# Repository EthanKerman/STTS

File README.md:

# STTS — Pocket Synth

A **behbeh** credit card sized synth for your wallet. The keys are a full octave ad you can go up and down 2 more. The noise from a piezo disc which is why theres a hole in the board.

## Features (this feels like a sales pitch lol)

- 13 touch keys (C to high C), octave down, octave up, and mode
- Three play modes of plain, arpeggio, vibrato
- Octave shift of ±2
- Differential piezo drive for hopefully double the volume of a normal buzzer
- Runs on one CR2016 coin cell, auto sleeps after 30 s, hold MODE to wake

## How it works

- **MCU:** ATtiny1617 (24 pin QFN), programmed over UPDI
- **Touch sensing:** each key is a copper pad under soldermask, connected to a MCU pin and to a shared TOUCH_SEND line on a 1 MΩ resistor. The firmware times how long each pad takes to charge a finger adds capacitance and makes it slower. Each pad is calibrated at power on.
- **Speaker:** a 15 mm piezo disc glued over a 10 mm hole, driven from two pins in opposite phase. Touch readings are timed between speaker transitions to avoid interference.
- **Power:** CR2016 → B5819W Schottky diode (blocks the programmer from back feeding the coin cell) → 10 µF + 100 nF decoupling.
- **Layout:** all components are on the back. Nothing sits behind the white keys, and no key's trace runs behind a different key, to keep keys from triggering each other.

## Repo layout

| Folder | Contents |

| `hardware/` | KiCad 9 project (schematic, PCB, custom footprints in `libs/`) |
| `firmware/STTS/` | Arduino sketch (megaTinyCore) |
| `production/` | Gerbers, BOM, and placement (CPL) files for JLCPCB |
| `images/` | Beautiful renders and screenshots |

## Bill of materials

Assembled by JLCPCB (Economic PCBA, bottom side), 5 boards.

Full BOM: bom.csv

Assembled by JLCPCB (Economic PCBA, bottom side), 5 boards.

Part	Qty per board	LCSC
ATtiny1617-MNR	1	C614176
1 MΩ 0603 resistor	16	C22935
10 µF 0805 capacitor	1	C15850
100 nF 0603 capacitor	1	C14663
B5819W Schottky diode	1	C8598
CR2016 SMD holder	1	C964740
15 mm piezo disc (hand-soldered)	1	—
Item	Cost (USD)
JLCPCB order (5 PCBs, assembly, components, shipping)	$52.12
Piezo discs	$5.00
3D-printed case (own printers)	$0.00
Total	$57.12

**JLCPCB quote (5 assembled boards, 0.8 mm): $52.12**

**Piezo discs (bought separately): $5**

**Total: $57.12**

## Building and flashing

1. Install the Arduino IDE and add **megaTinyCore** through the Boards Manager.
2. Settings: Chip **ATtiny1617**, Clock **5 MHz internal**, millis() timer **TCA0 or TCD0** (not TCB0, which drives the speaker), Programmer **SerialUPDI**.
3. Wire a 3.3 V USB serial adapter as a SerialUPDI programmer to the GND / UPDI / VCC pads on the back. **Take the coin cell out before connecting VCC.**
4. Run **Burn Bootloader** once to set the clock fuses, then **Upload**.

## Status

Schematic                                        yeye
PCB layout (DRC clean)                           yeye
Firmware v0.1 (compiles untested on hardware)    yeye
Front and back 3d printed covers                 yeye
Boards ordered                                   nono
Bring up and touch tuning                        nono

## Case

A two-piece 3D-printed case: the bottom piece holds the card, and the top piece slides on after it's in. There's also a bottom-only version that works as a back cover. The piezo has a clear window so it can still vibrate, and the touch keys stay exposed.

- STLs and STEP: `case/`
- Editable Onshape source: [Onshape document](https://cad.onshape.com/documents/209f1cf692407caf204aedcd/w/ec89c730faa0e29024759e87/e/6a25621725d754ed044dea4a)

## Notes

Designed by yours truly EthanKerman for [Hack Club Forge](https://forge.hackclub.com)

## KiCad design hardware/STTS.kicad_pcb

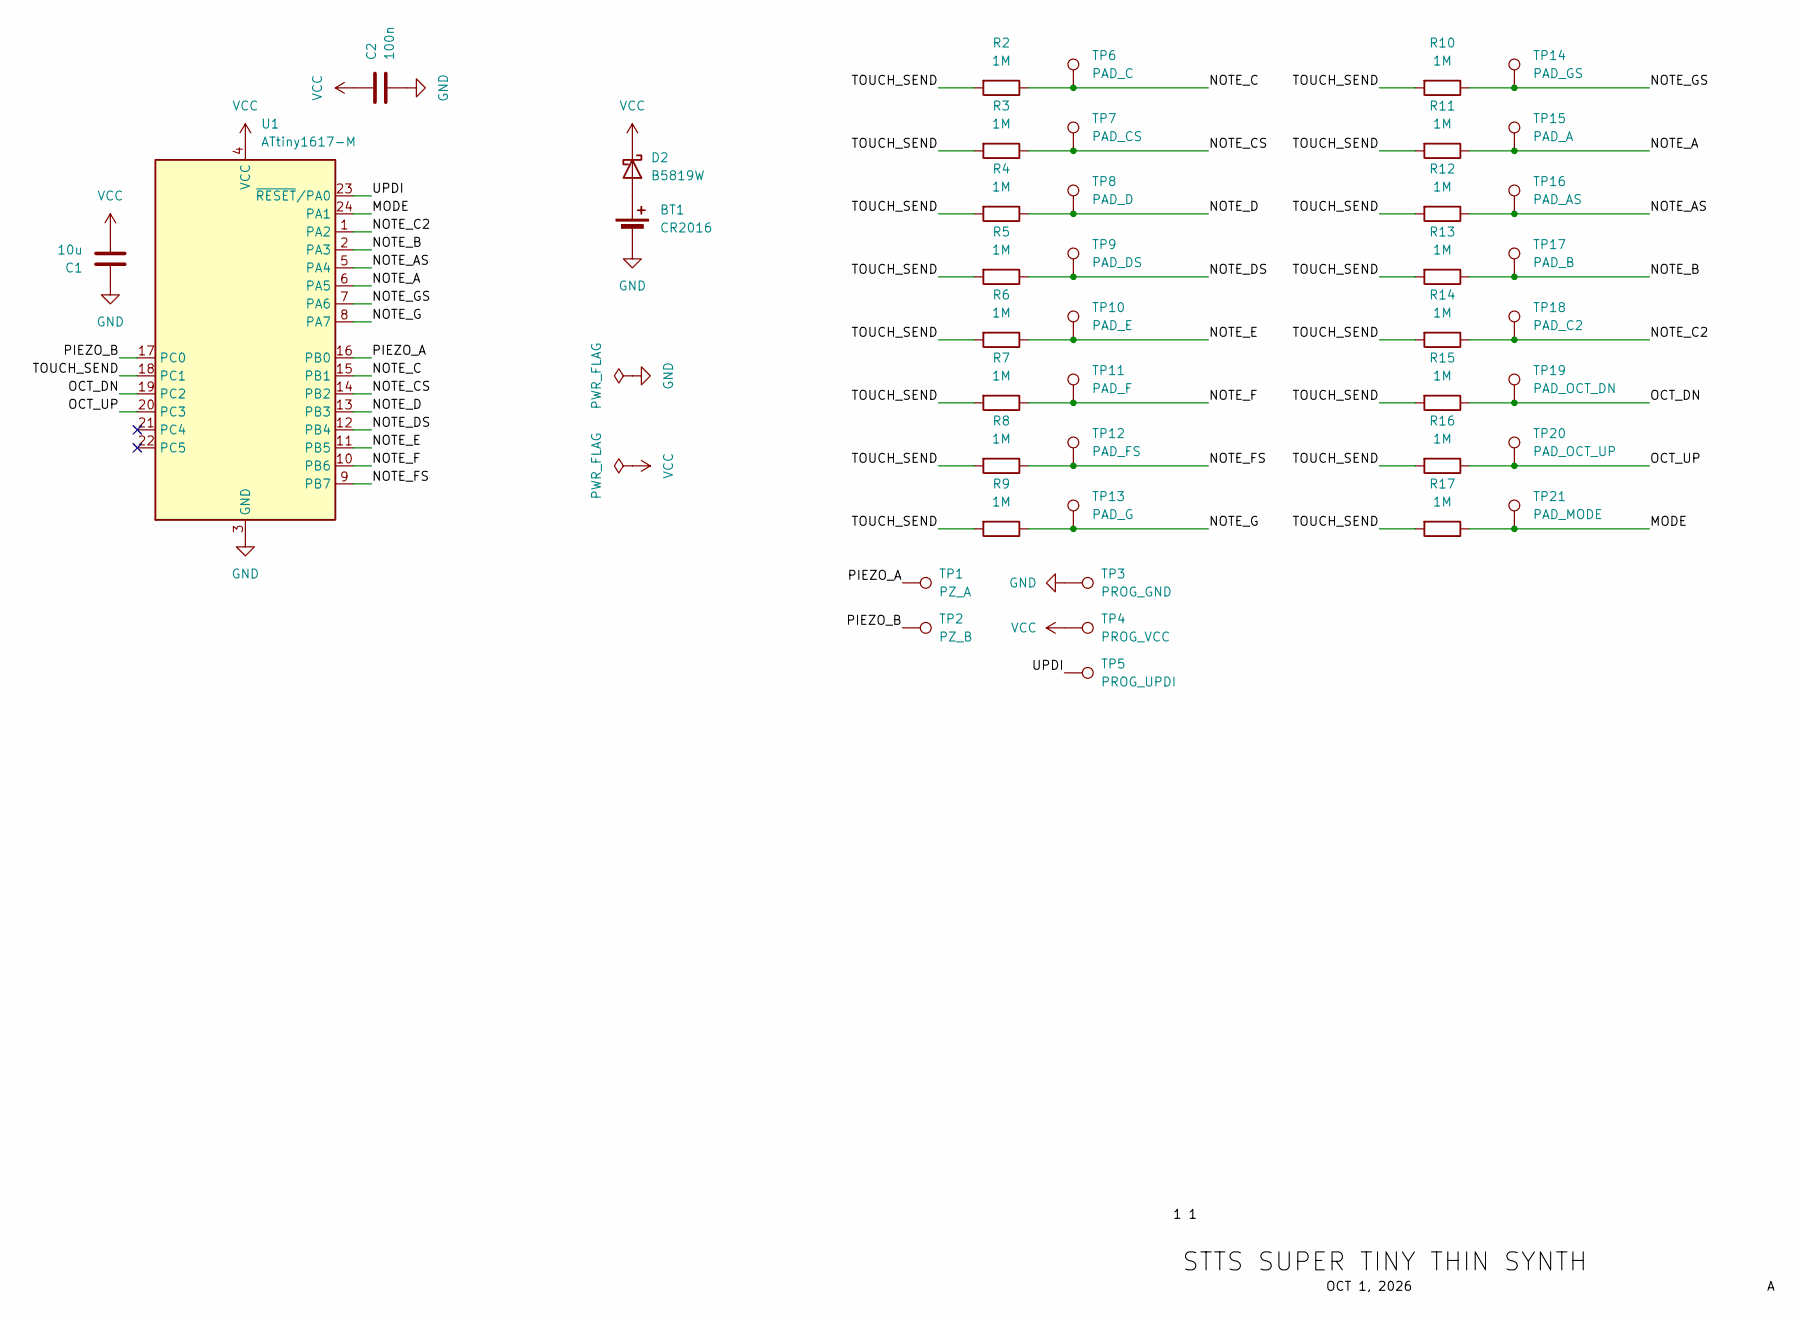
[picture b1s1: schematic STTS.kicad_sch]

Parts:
BT1: CR2016; BAT-SMD_BS-2016-B2AA001; LCSC C964740
C1: 10u; C_0805_2012Metric; LCSC C15850
C2: 100n; C_0603_1608Metric; LCSC C14663
D2: B5819W; D_SOD-123; LCSC C8598
R2, R3, R4, R5, R6, R7, R8, R9, R10, R11, R12, R13, R14, R15, R16, R17: 1M; R_0603_1608Metric; LCSC C22935
TP1: PZ_A; TestPoint_Pad_D2.0mm
TP2: PZ_B; TestPoint_Pad_D2.0mm
TP3: PROG_GND; TestPoint_Pad_D1.5mm
TP4: PROG_VCC; TestPoint_Pad_D1.5mm
TP5: PROG_UPDI; TestPoint_Pad_D1.5mm
TP6: PAD_C; TouchPad_White
TP7: PAD_CS; TouchPad_Black
TP8: PAD_D; TouchPad_White
TP9: PAD_DS; TouchPad_Black
TP10: PAD_E; TouchPad_White
TP11: PAD_F; TouchPad_White
TP12: PAD_FS; TouchPad_Black
TP13: PAD_G; TouchPad_White
TP14: PAD_GS; TouchPad_Black
TP15: PAD_A; TouchPad_White
TP16: PAD_AS; TouchPad_Black
TP17: PAD_B; TouchPad_White
TP18: PAD_C2; TouchPad_White
TP19: PAD_OCT_DN; TouchPad_Func
TP20: PAD_OCT_UP; TouchPad_Func
TP21: PAD_MODE; TouchPad_Func
U1: ATtiny1617-M; QFN-24-1EP_4x4mm_P0.5mm_EP2.6x2.6mm; LCSC C614176

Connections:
/MODE: R17.1, TP21.1, U1.24 (PA1)
/NOTE_A: R11.1, TP15.1, U1.6 (PA5)
/NOTE_AS: R12.1, TP16.1, U1.5 (PA4)
/NOTE_B: R13.1, TP17.1, U1.2 (PA3)
/NOTE_C: R2.1, TP6.1, U1.15 (PB1)
/NOTE_C2: R14.1, TP18.1, U1.1 (PA2)
/NOTE_CS: R3.1, TP7.1, U1.14 (PB2)
/NOTE_D: R4.1, TP8.1, U1.13 (PB3)
/NOTE_DS: R5.1, TP9.1, U1.12 (PB4)
/NOTE_E: R6.1, TP10.1, U1.11 (PB5)
/NOTE_F: R7.1, TP11.1, U1.10 (PB6)
/NOTE_FS: R8.1, TP12.1, U1.9 (PB7)
/NOTE_G: R9.1, TP13.1, U1.8 (PA7)
/NOTE_GS: R10.1, TP14.1, U1.7 (PA6)
/OCT_DN: R15.1, TP19.1, U1.19 (PC2)
/OCT_UP: R16.1, TP20.1, U1.20 (PC3)
/PIEZO_A: TP1.1, U1.16 (PB0)
/PIEZO_B: TP2.1, U1.17 (PC0)
/TOUCH_SEND: R2.2, R3.2, R4.2, R5.2, R6.2, R7.2, R8.2, R9.2, R10.2, R11.2, R12.2, R13.2, R14.2, R15.2, R16.2, R17.2, U1.18 (PC1)
/UPDI: TP5.1, U1.23 (~RESET/PA0)
GND: BT1.2 (-), C1.2, C2.2, TP3.1, U1.3 (GND), U1.25 (GND)
unnamed: BT1.1 (+), D2.2 (A)
VCC: C1.1, C2.1, D2.1 (K), TP4.1, U1.4 (VCC)

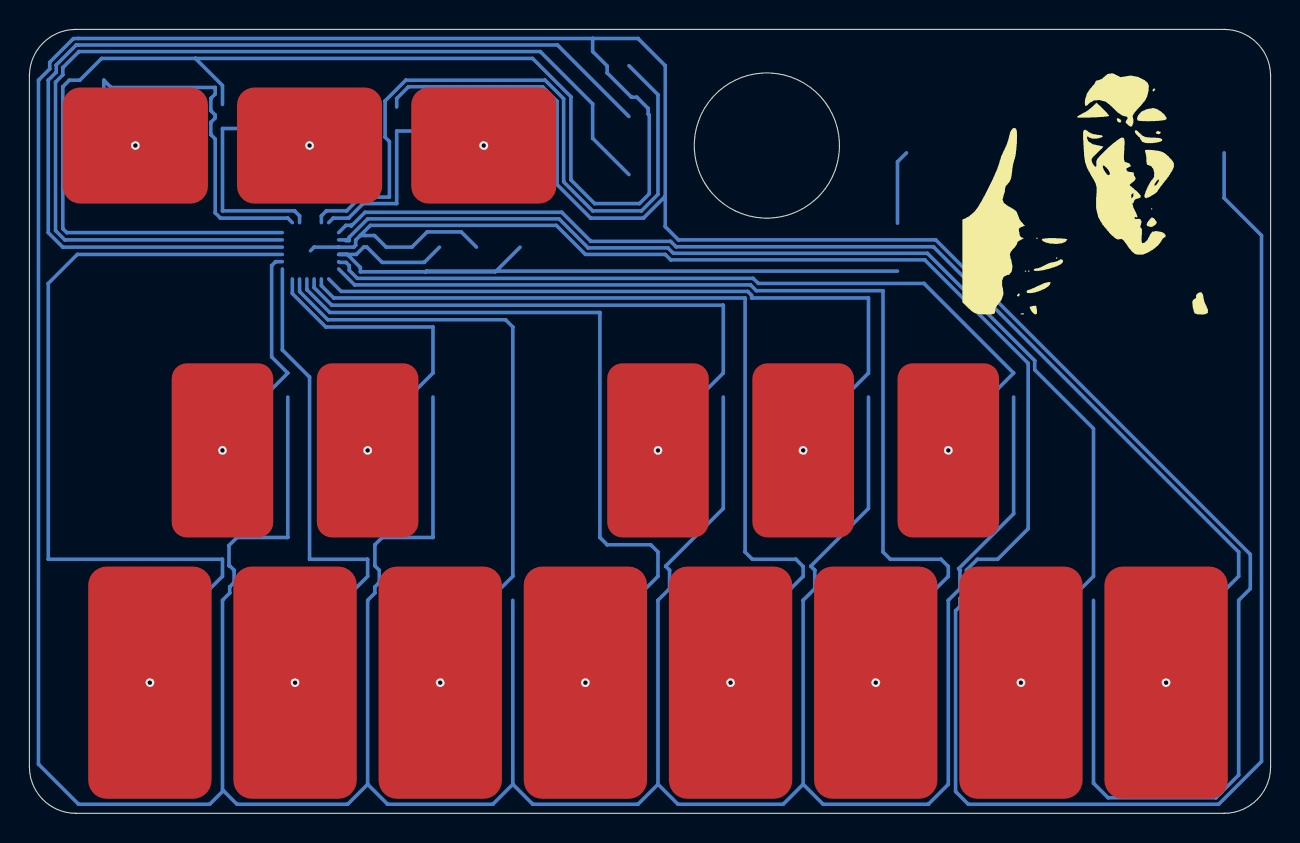
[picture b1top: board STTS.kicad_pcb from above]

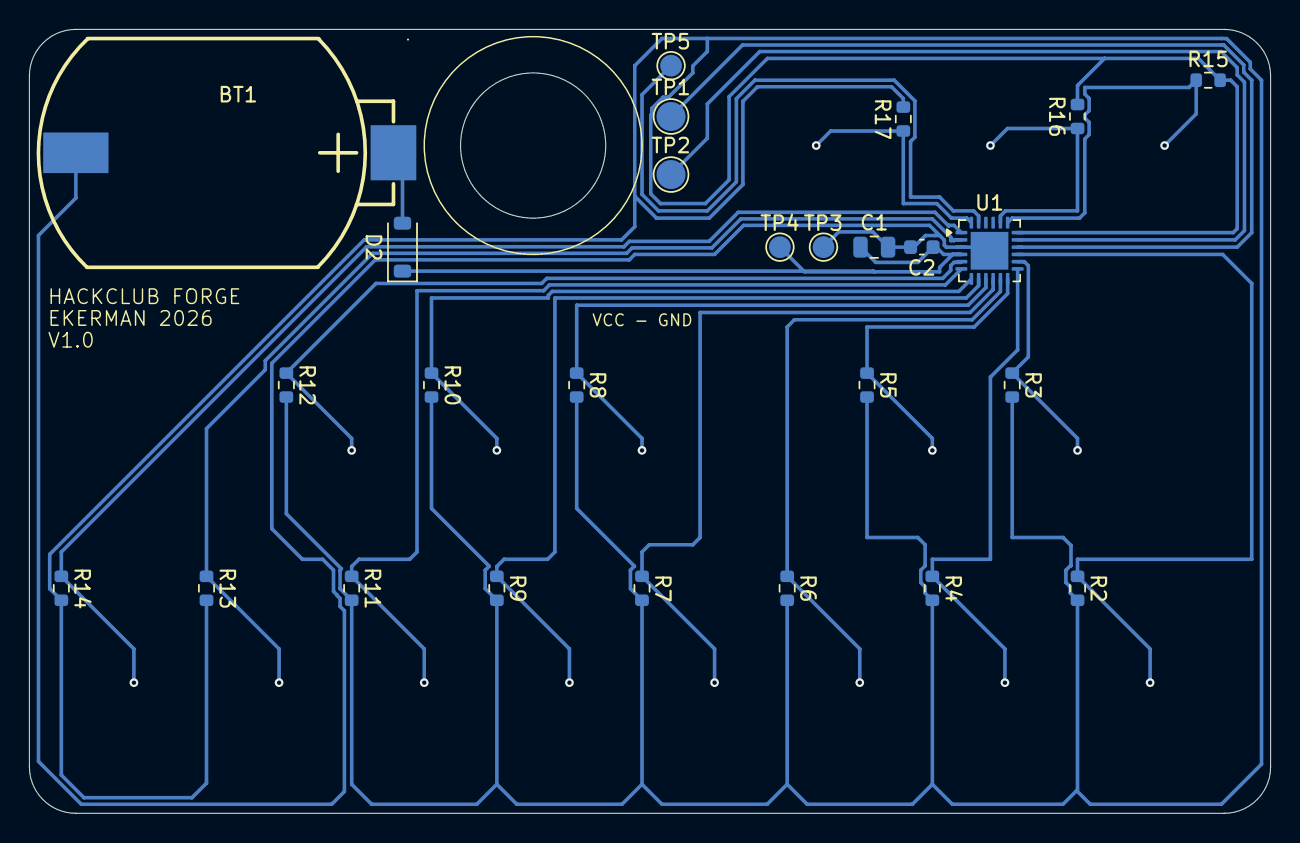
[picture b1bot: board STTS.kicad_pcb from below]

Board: 2 copper layers, 85.5 x 54.0 mm, 42 parts (26 on the bottom side), 23 nets.

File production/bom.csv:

Designator,Footprint,Quantity,Value,LCSC Part #
BT1,BAT-SMD_BS-2016-B2AA001,1,CR2016,C964740
C1,0805,1,10u,C15850
C2,0603,1,100n,C14663
D2,D_SOD-123,1,B5819W,C8598
"R10, R11, R12, R13, R14, R15, R16, R17, R2, R3, R4, R5, R6, R7, R8, R9",0603,16,1M,C22935
U1,QFN-24-1EP_4x4mm_P0.5mm_EP2.6x2.6mm,1,ATtiny1617-M,C614176

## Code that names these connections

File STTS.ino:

//         ___________________________________________________________________________________________
//        /                  |                         |                           /                  |
//       /                   |                         |                          /                   |
//      /                    |                         |                         /                    |
//     /              _______|_______           _______|_______         ________/              _______|
//    /              |               |         |              |         |      /              |
//    |              |_______        |         |              |         |      |              |_______       
//    |                      |       |         |              |         |      |                      |
//    |________              |       |         |              |         |      |________              |
//             |             |       |         |              |         |               |             |
//    _________|             /       |         |              |         |       ________|             /
//    |                     /        |         |              |         |      |                     /
//    |                    /         |         |              |         |      |                    /
//    |                   /          |         |              |         |      |                   /          STTS pocket synth firmware
//    |__________________/           |_________|              |_________|      |__________________/           v0.1

// ---------- Pins ----------
struct Pad {
  VPORT_t *vp;   
  uint8_t m;     
};


const Pad pads[16] = {
  {&VPORTB, PIN1_bm},  // 0  C
  {&VPORTB, PIN2_bm},  // 1  C#
  {&VPORTB, PIN3_bm},  // 2  D
  {&VPORTB, PIN4_bm},  // 3  D#
  {&VPORTB, PIN5_bm},  // 4  E
  {&VPORTB, PIN6_bm},  // 5  F
  {&VPORTB, PIN7_bm},  // 6  F#
  {&VPORTA, PIN7_bm},  // 7  G
  {&VPORTA, PIN6_bm},  // 8  G#
  {&VPORTA, PIN5_bm},  // 9  A
  {&VPORTA, PIN4_bm},  // 10 A#
  {&VPORTA, PIN3_bm},  // 11 B
  {&VPORTA, PIN2_bm},  // 12 high C
  {&VPORTC, PIN2_bm},  // 13 OCT_DN
  {&VPORTC, PIN3_bm},  // 14 OCT_UP
  {&VPORTA, PIN1_bm},  // 15 MODE
};

#define NUM_PADS   16
#define NUM_KEYS   13
#define PAD_OCT_DN 13
#define PAD_OCT_UP 14
#define PAD_MODE   15

#define SEND_M   PIN1_bm  
#define PIEZO_A  PIN0_bm   
#define PIEZO_B  PIN0_bm 

// ---------- Settings ----------
#define SAMPLES   16         
#define TIMEOUT   1000     
#define SLEEP_MS  30000UL    

// ---------- State ----------
volatile bool soundOn = false;
uint16_t baseline[NUM_PADS];
int8_t octave = 0;          
uint8_t mode = 0;           
uint32_t lastTouch = 0;
bool prevFn[3] = {false, false, false};


const uint16_t freq100[12] = {
  26163, 27718, 29366, 31113, 32963, 34923,
  36999, 39200, 41530, 44000, 46616, 49388
};

// ================= SPEAKER =================


ISR(TCB0_INT_vect) {
  TCB0.INTFLAGS = TCB_CAPT_bm;
  VPORTB.IN = PIEZO_A;  
  VPORTC.IN = PIEZO_B;
}

uint16_t ticksFor(int8_t semis) {      
  int8_t oct = 0;
  while (semis < 0)   { semis += 12; oct--; }
  while (semis >= 12) { semis -= 12; oct++; }
  uint32_t t = (F_CPU / 4) * 100UL / freq100[(uint8_t)semis];
  if (oct > 0) t >>= oct;
  if (oct < 0) t <<= -oct;
  if (t > 65000) t = 65000;
  if (t < 100) t = 100;
  return (uint16_t)t;
}

void soundStart(uint16_t ticks) {
  if (!soundOn) {
    VPORTB.OUT |= PIEZO_A;    
    VPORTC.OUT &= ~PIEZO_B;
    TCB0.CCMP = ticks;
    TCB0.CNT = 0;
    TCB0.INTCTRL = TCB_CAPT_bm;
    TCB0.CTRLA = TCB_CLKSEL_CLKDIV2_gc | TCB_ENABLE_bm;
    soundOn = true;
  } else {
    cli();
    TCB0.CCMP = ticks;
    if (TCB0.CNT >= ticks) TCB0.CNT = 0;
    sei();
  }
}

void soundStop() {
  TCB0.CTRLA = 0;
  TCB0.INTCTRL = 0;
  soundOn = false;
  VPORTB.OUT &= ~PIEZO_A;
  VPORTC.OUT &= ~PIEZO_B;
}

// ================= TOUCH =================

void waitQuiet() {
  if (!soundOn) return;
  if (TCB0.CCMP < 450) return;   
  while (true) {
    uint16_t c = TCB0.CNT;
    uint16_t top = TCB0.CCMP;
    if (c > 150 && (uint16_t)(top - c) > 250) return;
  }
}

uint16_t sensePad(uint8_t i) {
  VPORT_t *vp = pads[i].vp;
  uint8_t m = pads[i].m;
  uint16_t total = 0;

  for (uint8_t s = 0; s < SAMPLES; s++) {
    waitQuiet();
    cli();
    VPORTC.OUT &= ~SEND_M;    
    vp->OUT &= ~m;                  
    vp->DIR |= m;
    delayMicroseconds(4);
    vp->DIR &= ~m;              

    uint16_t t = 0;
    VPORTC.OUT |= SEND_M;         
    while (!(vp->IN & m) && t < TIMEOUT) t++;
    vp->OUT |= m;                 
    vp->DIR |= m;
    vp->DIR &= ~m;
    vp->OUT &= ~m;
    VPORTC.OUT &= ~SEND_M;          
    while ((vp->IN & m) && t < 2 * TIMEOUT) t++;
    sei();

    total += t;
  }
  return total;
}

uint16_t threshold(uint8_t i) {
  return baseline[i] / 8 + 8;       
}

void calibrate() {
  for (uint8_t i = 0; i < NUM_PADS; i++) baseline[i] = sensePad(i);
  for (uint8_t k = 0; k < 7; k++) {
    for (uint8_t i = 0; i < NUM_PADS; i++) {
      baseline[i] = (uint16_t)(((uint32_t)baseline[i] * 3 + sensePad(i)) / 4);
    }
  }
}

// ================= SLEEP =================

ISR(RTC_PIT_vect) {
  RTC.PITINTFLAGS = RTC_PI_bm;    
}

void goToSleep() {
  soundStop();

  VPORTC.OUT &= ~SEND_M;
  for (uint8_t i = 0; i < NUM_PADS; i++) {
    pads[i].vp->OUT &= ~pads[i].m;
    pads[i].vp->DIR |= pads[i].m;
  }

  // Baseline for MODE with the other pads held low
  pads[PAD_MODE].vp->DIR &= ~pads[PAD_MODE].m;
  uint16_t sleepBase = sensePad(PAD_MODE);
  uint16_t sleepThr = sleepBase / 8 + 8;
  pads[PAD_MODE].vp->DIR |= pads[PAD_MODE].m;

  while (RTC.STATUS > 0) {}
  RTC.CLKSEL = RTC_CLKSEL_INT32K_gc;
  while (RTC.PITSTATUS > 0) {}
  RTC.PITINTCTRL = RTC_PI_bm;
  RTC.PITCTRLA = RTC_PERIOD_CYC8192_gc | RTC_PITEN_bm;

  uint8_t hits = 0;
  while (hits < 2) {              
    SLPCTRL.CTRLA = SLPCTRL_SMODE_PDOWN_gc | SLPCTRL_SEN_bm;
    __asm__ __volatile__("sleep");
    SLPCTRL.CTRLA = 0;

    pads[PAD_MODE].vp->DIR &= ~pads[PAD_MODE].m;
    uint16_t r = sensePad(PAD_MODE);
    pads[PAD_MODE].vp->DIR |= pads[PAD_MODE].m;

    if (r > sleepBase + sleepThr) hits++;
    else hits = 0;
  }

  // Awake again
  while (RTC.PITSTATUS > 0) {}
  RTC.PITCTRLA = 0;
  for (uint8_t i = 0; i < NUM_PADS; i++) {
    pads[i].vp->DIR &= ~pads[i].m; 
  }
  prevFn[2] = true;               
  lastTouch = millis();

  soundStart(ticksFor(12));          
  delay(60);
  soundStop();
}

// ================= MAIN =================

void setup() {
  VPORTC.DIR |= SEND_M;
  VPORTC.OUT &= ~SEND_M;
  VPORTB.DIR |= PIEZO_A;
  VPORTC.DIR |= PIEZO_B;
  PORTC.PIN4CTRL = PORT_PULLUPEN_bm; 
  PORTC.PIN5CTRL = PORT_PULLUPEN_bm;
  for (uint8_t i = 0; i < NUM_PADS; i++) {
    pads[i].vp->DIR &= ~pads[i].m;
  }

  soundStart(ticksFor(0));  delay(80);
  soundStart(ticksFor(7));  delay(80);
  soundStart(ticksFor(12)); delay(120);
  soundStop();

  calibrate();                    
  lastTouch = millis();
}

void loop() {
  uint16_t raw[NUM_PADS];
  bool touched[NUM_PADS];
  bool any = false;

  for (uint8_t i = 0; i < NUM_PADS; i++) {
    raw[i] = sensePad(i);
    touched[i] = raw[i] > baseline[i] + threshold(i);
    if (touched[i]) {
      any = true;
    } else if (raw[i] < baseline[i] + threshold(i) / 2) {
      // slowly follow temperature and battery drift
      int32_t diff = (int32_t)raw[i] - (int32_t)baseline[i];
      baseline[i] = (uint16_t)((int32_t)baseline[i] + diff / 16);
    }
  }

  bool fn[3] = {touched[PAD_OCT_DN], touched[PAD_OCT_UP], touched[PAD_MODE]};
  if (fn[0] && !prevFn[0] && octave > -2) octave--;
  if (fn[1] && !prevFn[1] && octave < 2)  octave++;
  if (fn[2] && !prevFn[2]) mode = (mode + 1) % 3;
  for (uint8_t k = 0; k < 3; k++) prevFn[k] = fn[k];

  int8_t best = -1;
  uint16_t bestD = 0;
  for (uint8_t i = 0; i < NUM_KEYS; i++) {
    if (touched[i] && raw[i] - baseline[i] > bestD) {
      bestD = raw[i] - baseline[i];
      best = i;
    }
  }

  if (best >= 0) {
    int8_t semis = best + octave * 12;
    if (mode == 1) {                               
      const int8_t arp[4] = {0, 4, 7, 12};
      semis += arp[(millis() / 70) % 4];
    }
    uint16_t t = ticksFor(semis);
    if (mode == 2) {                                  
      int16_t v = (millis() / 8) % 32;
      v = (v < 16) ? v : 31 - v;
      t = (uint16_t)((int32_t)t + (int32_t)t * (v - 8) / 512);
    }
    soundStart(t);
  } else {
    soundStop();
  }

  if (any) lastTouch = millis();
  if (millis() - lastTouch > SLEEP_MS) goToSleep();
}
